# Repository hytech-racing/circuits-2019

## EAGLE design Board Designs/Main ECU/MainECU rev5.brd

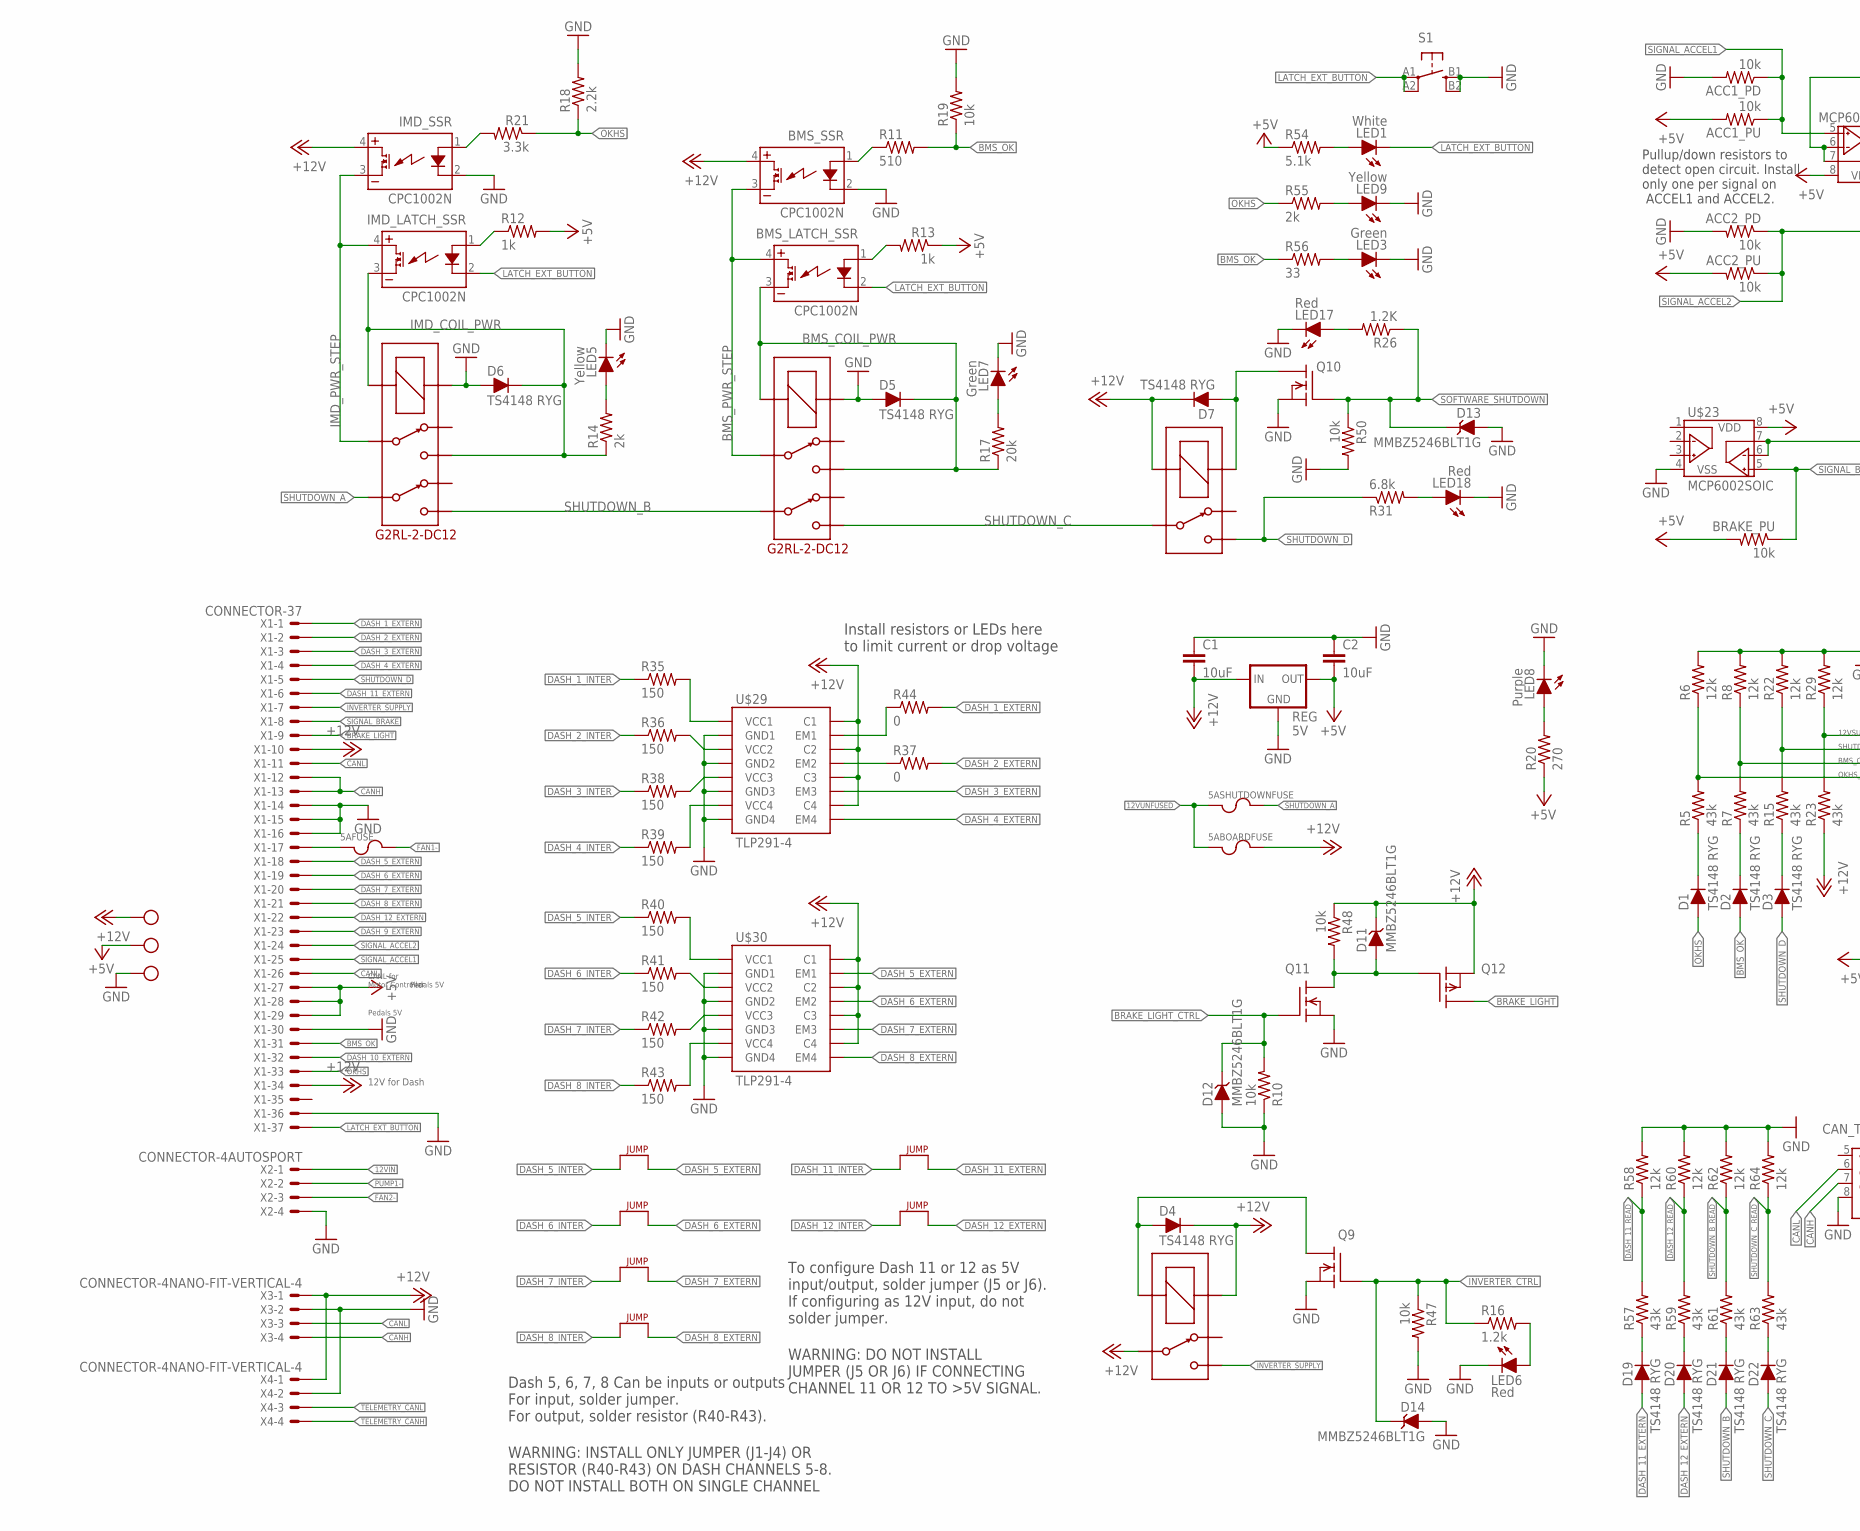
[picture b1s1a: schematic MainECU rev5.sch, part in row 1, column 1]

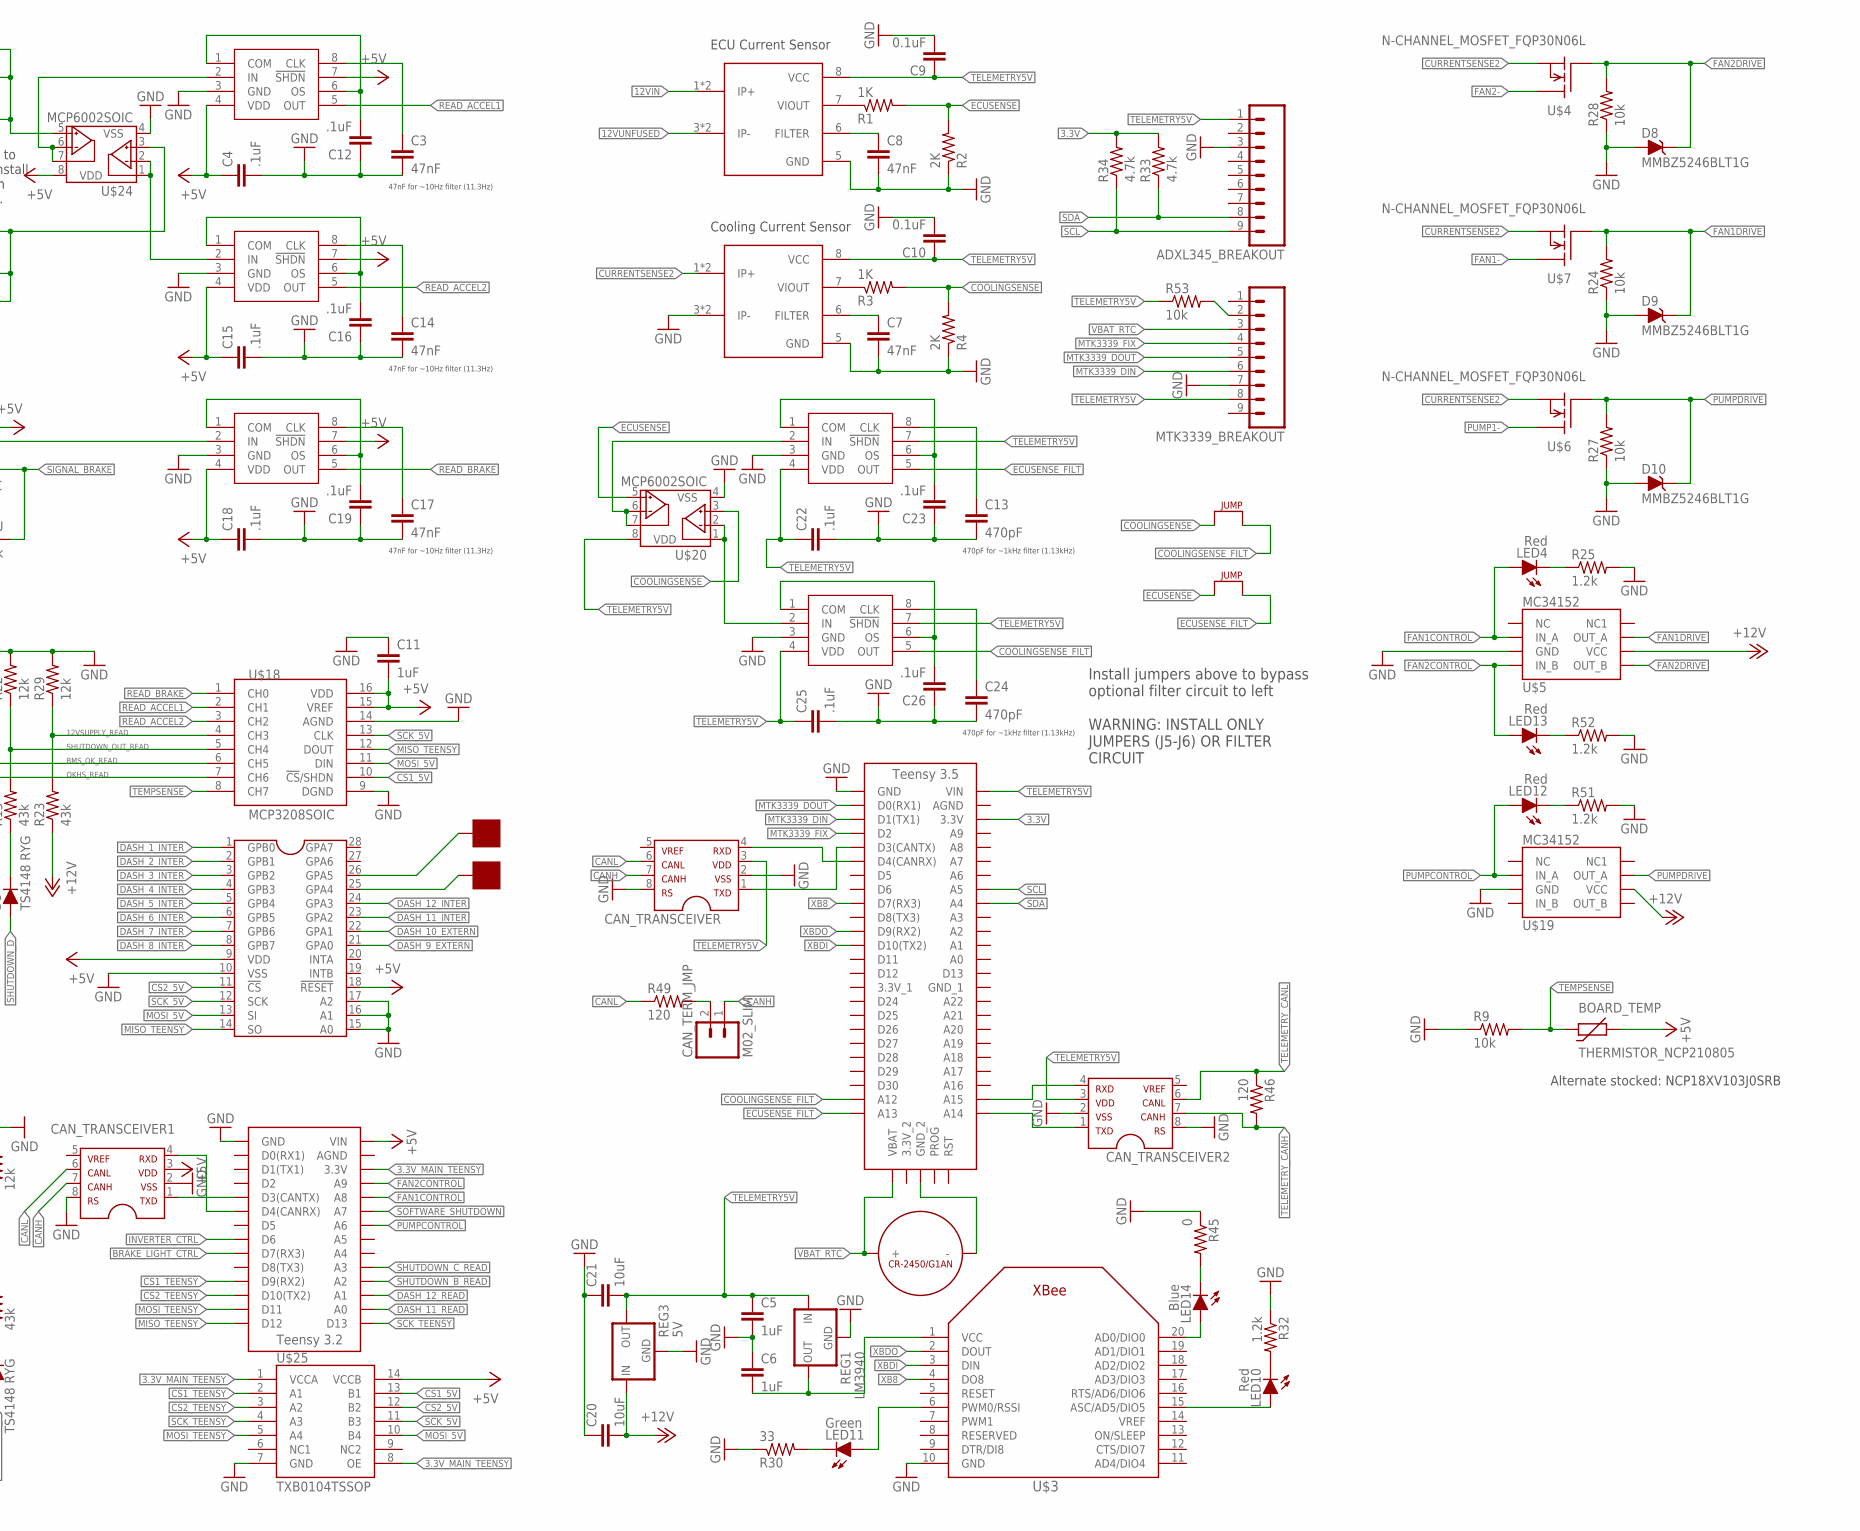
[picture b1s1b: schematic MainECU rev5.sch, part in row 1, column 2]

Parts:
5ABOARDFUSE, 5AFUSE, 5ASHUTDOWNFUSE: FUSE_MINIBLADE; MINI-BLADE_FUSE_HOLDER
ACC1_PD, ACC1_PU, ACC2_PD, ACC2_PU: 10k; 0805
ADXL345_BREAKOUT: M09; 1X09
BMS_LATCH_SSR: CPC1002N; SOP04
BMS_SSR: CPC1002N; SOP04
BOARD_TEMP: THERMISTOR_NCP210805; 0805
BRAKE_PU: 10k; 0805
C1, C2, C20, C21: 10uF; 0805
C3, C7, C8, C14, C17: 47nF; 0805
C4, C12, C15, C16, C18, C19, C22, C23, C25, C26: .1uF; 0805
C5, C6, C11: 1uF; 0805
C9, C10: 0.1uF; 0805
C13, C24: 470pF; 0805
CAN_TERM_JMP: M02_SLIM; 1X02_SLIM
CAN_TRANSCEIVER, CAN_TRANSCEIVER1, CAN_TRANSCEIVER2: MCP2551; SOIC-08
D1, D2, D3, D4, D5, D6, D7, D19, D20, D21, D22: TS4148 RYG; 0805_D
D8, D9, D10, D11, D12, D13, D14: MMBZ5246BLT1G; SOT23
IMD_LATCH_SSR: CPC1002N; SOP04
IMD_SHUTDOWN, IMD_SHUTDOWN1: G2RL-2-DC12; G2RL-2
IMD_SSR: CPC1002N; SOP04
INVERTER_PWR_RELAY: G5LE; ZF112
J1, J2, J3, J4, J5, J6, J7, J8: JUMPER; 0805
LED1: White; LED-805
LED3, LED7, LED11: Green; LED-805
LED4, LED6, LED10, LED12, LED13, LED17, LED18: Red; LED-805
LED5, LED9: Yellow; LED-805
LED8: Purple; LED-805
LED14: Blue; LED-805
MTK3339_BREAKOUT: M09; 1X09
P1, P2: SOLDER_PAD; SOLDER_PAD_XSMALL
Q9, Q10, Q11: DMG3406LSOT; SOT23
Q12: P-CHANNEL_MOSFET_DMP3099L-7; SOT23
R1, R3: 1K; 0805
R2, R4: 2K; 0805
R5, R7, R15, R23, R57, R59, R61, R63: 43k; 0805
R6, R8, R22, R29, R58, R60, R62, R64: 12k; 0805
R9, R10, R19, R24, R27, R28, R47, R48, R50, R53: 10k; 0805
R11: 510; 0805
R12, R13: 1k; 0805
R14, R55: 2k; 0805
R16, R25, R32, R51, R52: 1.2k; 0805
R17: 20k; 0805
R18: 2.2k; 0805
R20: 270; 0805
R21: 3.3k; 0805
R26: 1.2K; 0805
R30, R56: 33; 0805
R31: 6.8k; 0805
R33, R34: 4.7k; 0805
R35, R36, R38, R39, R40, R41, R42, R43: 150; 0805
R37, R44, R45: 0; 0805
R46, R49: 120; 0805
R54: 5.1k; 0805
REG, REG3: 5V; OKI-78SR
REG1: LM3940; SOT223
S1: BTN_10-XXSMD; TACTILE_SWITCH_SMD_6.2MM_TALL
SOFTWARE_SHUTOFF: G5LE; ZF112
U$1: TEENSY_3.2_SIMPLE
U$2: TEENSY_3.5_EXT
U$3: XBEE
U$4, U$6, U$7: N-CHANNEL_MOSFET_FQP30N06L; TO-220-H-HOLE
U$5, U$19: MC34152; SOIC-08
U$8, U$11, U$12: TEST_POINT
U$9, U$10: ACS715_CURRENT_SENSOR; SOP8
U$16: CR-2450/G1AN
U$17: MCP23S17SSOP28; SSOP28
U$18: MCP3208SOIC; SOIC-16
U$20, U$23, U$24: MCP6002SOIC; SOIC-08
U$21, U$22, U$26, U$27, U$28: MAX7480; SOIC-08
U$25: TXB0104TSSOP; TSSOP-14
U$29, U$30: TLP291-4; 11-11F1
X1: CONNECTOR-37; AUTOSPORT_14-35
X2: CONNECTOR-4AUTOSPORT; AUTOSPORT_12-04
X3, X4: CONNECTOR-4NANO-FIT-VERTICAL-4; NANO-FIT_VERTICAL-4

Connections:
3.3V: R33.2, R34.2, U$2.3.3V
3.3V_MAIN_TEENSY: U$1.3.3V, U$25.1 (VCCA), U$25.8 (OE)
12VIN: U$9.1 (IP+), U$9.2 (IP+), X2.P$1
12VSUPPLY_READ: R23.2, R29.1, U$18.4 (CH3)
12VUNFUSED: 5ABOARDFUSE.L1 (1), 5ABOARDFUSE.L2 (1), 5ASHUTDOWNFUSE.L1 (1), 5ASHUTDOWNFUSE.L2 (1), U$9.3 (IP-), U$9.4 (IP-)
+5V: ACC1_PU.2, ACC2_PU.2, BOARD_TEMP.1, BRAKE_PU.2, C2.2, C4.1, C11.2, C15.1, C18.1, CAN_TRANSCEIVER1.3, R12.2, R13.1, R20.1, R54.1, REG.3 (OUT), U$1.VIN, U$11.P$1, U$17.9 (VDD), U$17.18 (!RESET), U$18.15 (VREF), U$18.16 (VDD), U$23.8 (VDD), U$24.8 (VDD), U$25.14 (VCCB), U$26.4 (VDD), U$26.7 (!SHDN), U$27.4 (VDD), U$27.7 (!SHDN), U$28.4 (VDD), U$28.7 (!SHDN), X1.P$27, X1.P$28, X1.P$29
+12V: 5ABOARDFUSE.R1 (2), 5ABOARDFUSE.R2 (2), BMS_SSR.4 (DC+), C1.2, C20.2, D4.C, D7.C, D11.3 (C), IMD_SSR.4 (DC+), INVERTER_PWR_RELAY.1 (COIL+), INVERTER_PWR_RELAY.P, Q12.2 (S), R23.1, R48.1, REG.1 (IN), REG3.1 (IN), SOFTWARE_SHUTOFF.2 (COIL-), U$5.6 (VCC), U$8.P$1, U$19.6 (VCC), U$29.10 (C4), U$29.12 (C3), U$29.14 (C2), U$29.16 (C1), U$30.10 (C4), U$30.12 (C3), U$30.14 (C2), U$30.16 (C1), X1.P$10, X1.P$34, X3.P$1, X4.P$1
BMS_COIL_PWR: BMS_LATCH_SSR.3 (DC-), D5.C, IMD_SHUTDOWN1.4, IMD_SHUTDOWN1.COIL-, R17.1
BMS_OK: D2.A, R11.2, R19.1, R56.1, X1.P$31
BMS_OK_READ: R7.2, R8.1, U$18.6 (CH5)
BMS_PWR_STEP: BMS_LATCH_SSR.4 (DC+), BMS_SSR.3 (DC-), IMD_SHUTDOWN1.3
BRAKE_LIGHT: Q12.3 (D), X1.P$9
BRAKE_LIGHT_CTRL: D12.3 (C), Q11.1 (G), R10.2, U$1.D7(RX3)
CANH: CAN_TERM_JMP.1, CAN_TRANSCEIVER.7, CAN_TRANSCEIVER1.7, X1.P$12, X1.P$13, X3.P$4
CANL: CAN_TRANSCEIVER.6, CAN_TRANSCEIVER1.6, R49.1, X1.P$11, X1.P$26, X3.P$3
COOLINGSENSE: J5.2, R3.2, R4.2, U$20.3 (VINA+)
COOLINGSENSE_FILT: J5.1, U$2.A12, U$22.5 (OUT)
CS1_5V: U$18.10 (!CS!/SHDN), U$25.13 (B1)
CS1_TEENSY: U$1.D9(RX2), U$25.2 (A1)
CS2_5V: U$17.11 (!CS), U$25.12 (B2)
CS2_TEENSY: U$1.D10(TX2), U$25.3 (A2)
CURRENTSENSE2: U$4.3 (S), U$6.3 (S), U$7.3 (S), U$10.1 (IP+), U$10.2 (IP+)
DASH_1_EXTERN: R44.2, X1.P$1
DASH_1_INTER: R35.1, U$17.1 (GPB0)
DASH_2_EXTERN: R37.2, X1.P$2
DASH_2_INTER: R36.1, U$17.2 (GPB1)
DASH_3_EXTERN: U$29.11 (EM3), X1.P$3
DASH_3_INTER: R38.1, U$17.3 (GPB2)
DASH_4_EXTERN: U$29.9 (EM4), X1.P$4
DASH_4_INTER: R39.1, U$17.4 (GPB3)
DASH_5_EXTERN: J1.1, U$30.15 (EM1), X1.P$18
DASH_5_INTER: J1.2, R40.1, U$17.5 (GPB4)
DASH_6_EXTERN: J2.1, U$30.13 (EM2), X1.P$19
DASH_6_INTER: J2.2, R41.1, U$17.6 (GPB5)
DASH_7_EXTERN: J3.1, U$30.11 (EM3), X1.P$20
DASH_7_INTER: J3.2, R42.1, U$17.7 (GPB6)
DASH_8_EXTERN: J4.1, U$30.9 (EM4), X1.P$21
DASH_8_INTER: J4.2, R43.1, U$17.8 (GPB7)
DASH_9_EXTERN: U$17.21 (GPA0), X1.P$23
DASH_10_EXTERN: U$17.22 (GPA1), X1.P$32
DASH_11_EXTERN: D19.A, J8.1, X1.P$6
DASH_11_INTER: J8.2, U$17.23 (GPA2)
DASH_11_READ: R57.2, R58.1, U$1.A0
DASH_12_EXTERN: D20.A, J7.1, X1.P$22
DASH_12_INTER: J7.2, U$17.24 (GPA3)
DASH_12_READ: R59.2, R60.1, U$1.A1
ECUSENSE: J6.2, R1.2, R2.2, U$20.5 (VINB+)
ECUSENSE_FILT: J6.1, U$2.A13, U$21.5 (OUT)
FAN1-: 5AFUSE.R1 (2), 5AFUSE.R2 (2), U$7.2 (D)
FAN1CONTROL: LED4.A, U$1.A8, U$5.2 (IN_A)
FAN1DRIVE: D9.3 (C), R24.2, U$5.7 (OUT_A), U$7.1 (G)
FAN2-: U$4.2 (D), X2.P$3
FAN2CONTROL: LED13.A, U$1.A9, U$5.4 (IN_B)
FAN2DRIVE: D8.3 (C), R28.2, U$4.1 (G), U$5.5 (OUT_B)
GND: ACC1_PD.2, ACC2_PD.2, ADXL345_BREAKOUT.3, BMS_SSR.2 (CONTROL-), C1.1, C2.1, C3.2, C4.2, C5.2, C6.1, C7.2, C8.2, C9.2, C10.2, C11.1, C12.1, C13.2, C14.2, C15.2, C16.1, C17.2, C18.2, C19.1, C20.1, C21.1, C22.2, C23.1, C24.2, C25.2, C26.1, CAN_TRANSCEIVER.2, CAN_TRANSCEIVER.8, CAN_TRANSCEIVER1.2, CAN_TRANSCEIVER1.8, CAN_TRANSCEIVER2.2, CAN_TRANSCEIVER2.8, D5.A, D6.A, D8.1 (A), D9.1 (A), D10.1 (A), D12.1 (A), D13.1 (A), D14.1 (A), IMD_SHUTDOWN.COIL+, IMD_SHUTDOWN1.COIL+, IMD_SSR.2 (CONTROL-), LED3.C, LED5.C, LED6.C, LED7.C, LED8.C, LED9.C, LED17.C, LED18.C, MTK3339_BREAKOUT.7, Q9.2 (S), Q10.2 (S), Q11.2 (S), R2.1, R4.1, R6.2, R8.2, R9.1, R10.1, R18.2, R19.2, R22.2, R24.1, R25.2, R27.1, R28.1, R29.2, R30.1, R32.1, R45.1, R47.2, R50.2, R51.2, R52.2, R58.2, R60.2, R62.2, R64.2, REG.2 (GND), REG1.2 (GND), REG1.4 (GND), REG3.2 (GND), S1.B1 (S), S1.B2 (S1), U$1.GND, U$2.GND, U$3.10 (GND), U$5.3 (GND), U$9.5 (GND), U$10.3 (IP-), U$10.4 (IP-), U$10.5 (GND), U$12.P$1, U$17.10 (VSS), U$17.15 (A0), U$17.16 (A1), U$17.17 (A2), U$18.9 (DGND), U$18.14 (AGND), U$19.3 (GND), U$20.4 (VSS), U$21.3 (GND), U$22.3 (GND), U$23.4 (VSS), U$24.4 (VSS), U$25.7 (GND), U$26.3 (GND), U$27.3 (GND), U$28.3 (GND), U$29.2 (GND1), U$29.4 (GND2), U$29.6 (GND3), U$29.8 (GND4), U$30.2 (GND1), U$30.4 (GND2), U$30.6 (GND3), U$30.8 (GND4), X1.P$14, X1.P$15, X1.P$16, X1.P$30, X1.P$36, X2.P$4, X3.P$2, X4.P$2
IMD_COIL_PWR: D6.C, IMD_LATCH_SSR.3 (DC-), IMD_SHUTDOWN.4, IMD_SHUTDOWN.COIL-, R14.1
IMD_PWR_STEP: IMD_LATCH_SSR.4 (DC+), IMD_SHUTDOWN.3, IMD_SSR.3 (DC-)
INVERTER_CTRL: D14.3 (C), Q9.1 (G), R16.1, R47.1, U$1.D6
INVERTER_SUPPLY: INVERTER_PWR_RELAY.S, X1.P$7
LATCH_EXT_BUTTON: BMS_LATCH_SSR.2 (CONTROL-), IMD_LATCH_SSR.2 (CONTROL-), LED1.C, S1.A1, S1.A2 (P1), X1.P$37
MISO_TEENSY: U$1.D12, U$17.14 (SO), U$18.12 (DOUT)
MOSI_5V: U$17.13 (SI), U$18.11 (DIN), U$25.10 (B4)
MOSI_TEENSY: U$1.D11, U$25.5 (A4)
MTK3339_DIN: MTK3339_BREAKOUT.6, U$2.D1(TX1)
MTK3339_DOUT: MTK3339_BREAKOUT.5, U$2.D0(RX1)
MTK3339_FIX: MTK3339_BREAKOUT.4, U$2.D2
unnamed: 5AFUSE.L1 (1), 5AFUSE.L2 (1), X1.P$17
unnamed: LED1.A, R54.2
unnamed: R1.1, U$9.7 (VIOUT)
unnamed: C12.2, U$27.1 (COM), U$27.6 (OS)
unnamed: IMD_LATCH_SSR.1 (CONTROL+), R12.1
unnamed: R3.1, U$10.7 (VIOUT)
unnamed: MTK3339_BREAKOUT.2, R53.2
unnamed: C8.1, U$9.6 (FILTER)
unnamed: LED3.A, R56.2
unnamed: D1.C, R5.1
unnamed: D2.C, R7.1
unnamed: BMS_LATCH_SSR.1 (CONTROL+), R13.2
unnamed: CAN_TRANSCEIVER.4, U$2.D4(CANRX)
unnamed: CAN_TRANSCEIVER.1, U$2.D3(CANTX)
unnamed: CAN_TRANSCEIVER1.4, U$1.D4(CANRX)
unnamed: D19.C, R57.1
unnamed: CAN_TERM_JMP.2, R49.2
unnamed: BMS_SSR.1 (CONTROL+), R11.1
unnamed: LED5.A, R14.2
unnamed: U$20.1 (VOUTA), U$20.2 (VINA-), U$22.2 (IN)
unnamed: C3.1, U$27.8 (CLK)
unnamed: CAN_TRANSCEIVER1.1, U$1.D3(CANTX)
unnamed: U$24.1 (VOUTA), U$24.2 (VINA-), U$28.2 (IN)
unnamed: U$24.6 (VINB-), U$24.7 (VOUTB), U$27.2 (IN)
unnamed: U$23.6 (VINB-), U$23.7 (VOUTB), U$26.2 (IN)
unnamed: LED9.A, R55.2
unnamed: D7.A, Q10.3 (D), SOFTWARE_SHUTOFF.1 (COIL+)
unnamed: LED6.A, R16.2
unnamed: LED8.A, R20.2
unnamed: R36.2, U$29.3 (VCC2)
unnamed: IMD_SSR.1 (CONTROL+), R21.2
unnamed: LED7.A, R17.2
unnamed: D3.C, R15.1
unnamed: D20.C, R59.1
unnamed: LED14.C, R45.2
unnamed: C16.2, U$28.1 (COM), U$28.6 (OS)
unnamed: C19.2, U$26.1 (COM), U$26.6 (OS)
unnamed: C14.1, U$28.8 (CLK)
unnamed: U$20.6 (VINB-), U$20.7 (VOUTB), U$21.2 (IN)
unnamed: LED18.A, R31.2
unnamed: C17.1, U$26.8 (CLK)
unnamed: R37.1, U$29.13 (EM2)
unnamed: C23.2, U$21.1 (COM), U$21.6 (OS)
unnamed: C13.1, U$21.8 (CLK)
unnamed: LED11.C, R30.2
unnamed: LED17.A, R26.2
unnamed: LED11.A, U$3.6 (PWM0/RSSI)
unnamed: C7.1, U$10.6 (FILTER)
unnamed: LED10.A, U$3.15 (ASC/AD5/DIO5)
unnamed: LED10.C, R32.2
unnamed: R35.2, U$29.1 (VCC1)
unnamed: R38.2, U$29.5 (VCC3)
unnamed: R39.2, U$29.7 (VCC4)
unnamed: R40.2, U$30.1 (VCC1)
unnamed: R41.2, U$30.3 (VCC2)
unnamed: R42.2, U$30.5 (VCC3)
unnamed: R43.2, U$30.7 (VCC4)
unnamed: D11.1 (A), Q11.3 (D), Q12.1 (G), R48.2
unnamed: R44.1, U$29.15 (EM1)
unnamed: D21.C, R61.1
unnamed: U$2.GND_2, U$16.-
unnamed: CAN_TRANSCEIVER2.4, U$2.A15
unnamed: LED14.A, U$3.20 (AD0/DIO0)
unnamed: CAN_TRANSCEIVER2.1, U$2.A14
unnamed: D22.C, R63.1
unnamed: D4.A, INVERTER_PWR_RELAY.2 (COIL-), Q9.3 (D)
unnamed: C26.2, U$22.1 (COM), U$22.6 (OS)
unnamed: C24.1, U$22.8 (CLK)
unnamed: LED4.C, R25.1
unnamed: LED12.C, R51.1
unnamed: LED13.C, R52.1
unnamed: P1.P$1, U$17.25 (GPA4)
unnamed: P2.P$1, U$17.26 (GPA5)
OKHS: D1.A, R18.1, R21.1, R55.1, X1.P$33
OKHS_READ: R5.2, R6.1, U$18.7 (CH6)
PUMP1-: U$6.2 (D), X2.P$2
PUMPCONTROL: LED12.A, U$1.A6, U$19.2 (IN_A)
PUMPDRIVE: D10.3 (C), R27.2, U$6.1 (G), U$19.7 (OUT_A)
READ_ACCEL1: U$18.2 (CH1), U$27.5 (OUT)
READ_ACCEL2: U$18.3 (CH2), U$28.5 (OUT)
READ_BRAKE: U$18.1 (CH0), U$26.5 (OUT)
SCK_5V: U$17.12 (SCK), U$18.13 (CLK), U$25.11 (B3)
SCK_TEENSY: U$1.D13, U$25.4 (A3)
SCL: ADXL345_BREAKOUT.9, R34.1, U$2.A5
SDA: ADXL345_BREAKOUT.8, R33.1, U$2.A4
SHUTDOWN_A: 5ASHUTDOWNFUSE.R1 (2), 5ASHUTDOWNFUSE.R2 (2), IMD_SHUTDOWN.6
SHUTDOWN_B: D21.A, IMD_SHUTDOWN.5, IMD_SHUTDOWN1.6
SHUTDOWN_B_READ: R61.2, R62.1, U$1.A2
SHUTDOWN_C: D22.A, IMD_SHUTDOWN1.5, SOFTWARE_SHUTOFF.P
SHUTDOWN_C_READ: R63.2, R64.1, U$1.A3
SHUTDOWN_D: D3.A, R31.1, SOFTWARE_SHUTOFF.S, X1.P$5
SHUTDOWN_OUT_READ: R15.2, R22.1, U$18.5 (CH4)
SIGNAL_ACCEL1: ACC1_PD.1, ACC1_PU.1, U$24.5 (VINB+), X1.P$25
SIGNAL_ACCEL2: ACC2_PD.1, ACC2_PU.1, U$24.3 (VINA+), X1.P$24
SIGNAL_BRAKE: BRAKE_PU.1, U$23.5 (VINB+), X1.P$8
SOFTWARE_SHUTDOWN: D13.3 (C), Q10.1 (G), R26.1, R50.1, U$1.A7
TELEMETRY5V: ADXL345_BREAKOUT.1, C5.1, C9.1, C10.1, C21.2, C22.1, C25.1, CAN_TRANSCEIVER.3, CAN_TRANSCEIVER2.3, MTK3339_BREAKOUT.8, R53.1, REG1.1 (IN), REG3.3 (OUT), U$2.VIN, U$9.8 (VCC), U$10.8 (VCC), U$20.8 (VDD), U$21.4 (VDD), U$21.7 (!SHDN), U$22.4 (VDD), U$22.7 (!SHDN)
TELEMETRY_CANH: CAN_TRANSCEIVER2.7, R46.2, X4.P$4
TELEMETRY_CANL: CAN_TRANSCEIVER2.6, R46.1, X4.P$3
TEMPSENSE: BOARD_TEMP.2, R9.2, U$18.8 (CH7)
VBAT_RTC: MTK3339_BREAKOUT.3, U$2.VBAT, U$16.+_0 (+), U$16.+_1 (+)
VCC: C6.2, REG1.3 (OUT), U$3.1 (VCC)
XB8: U$2.D7(RX3), U$3.4 (DO8)
XBDI: U$2.D10(TX2), U$3.3 (DIN)
XBDO: U$2.D9(RX2), U$3.2 (DOUT)

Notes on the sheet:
ECU Current Sensor
Cooling Current Sensor
Pullup/down resistors to detect open circuit. Install only one per signal on ACCEL1 and ACCEL2.
Pedals 5V
CANL for Motor Controller
47nF for ~10Hz filter (11.3Hz)
12V for Dash
Dash 5, 6, 7, 8 Can be inputs or outputs For input, solder jumper. For output, solder resistor (R40-R43).
470pF for ~1kHz filter (1.13kHz)
Install resistors or LEDs here to limit current or drop voltage
WARNING: INSTALL ONLY JUMPER (J1-J4) OR RESISTOR (R40-R43) ON DASH CHANNELS 5-8. DO NOT INSTALL BOTH ON SINGLE CHANNEL
Alternate stocked: NCP18XV103J0SRB
Install jumpers above to bypass optional filter circuit to left WARNING: INSTALL ONLY JUMPERS (J5-J6) OR FILTER CIRCUIT
To configure Dash 11 or 12 as 5V input/output, solder jumper (J5 or J6). If configuring as 12V input, do not solder jumper.
WARNING: DO NOT INSTALL JUMPER (J5 OR J6) IF CONNECTING CHANNEL 11 OR 12 TO >5V SIGNAL.

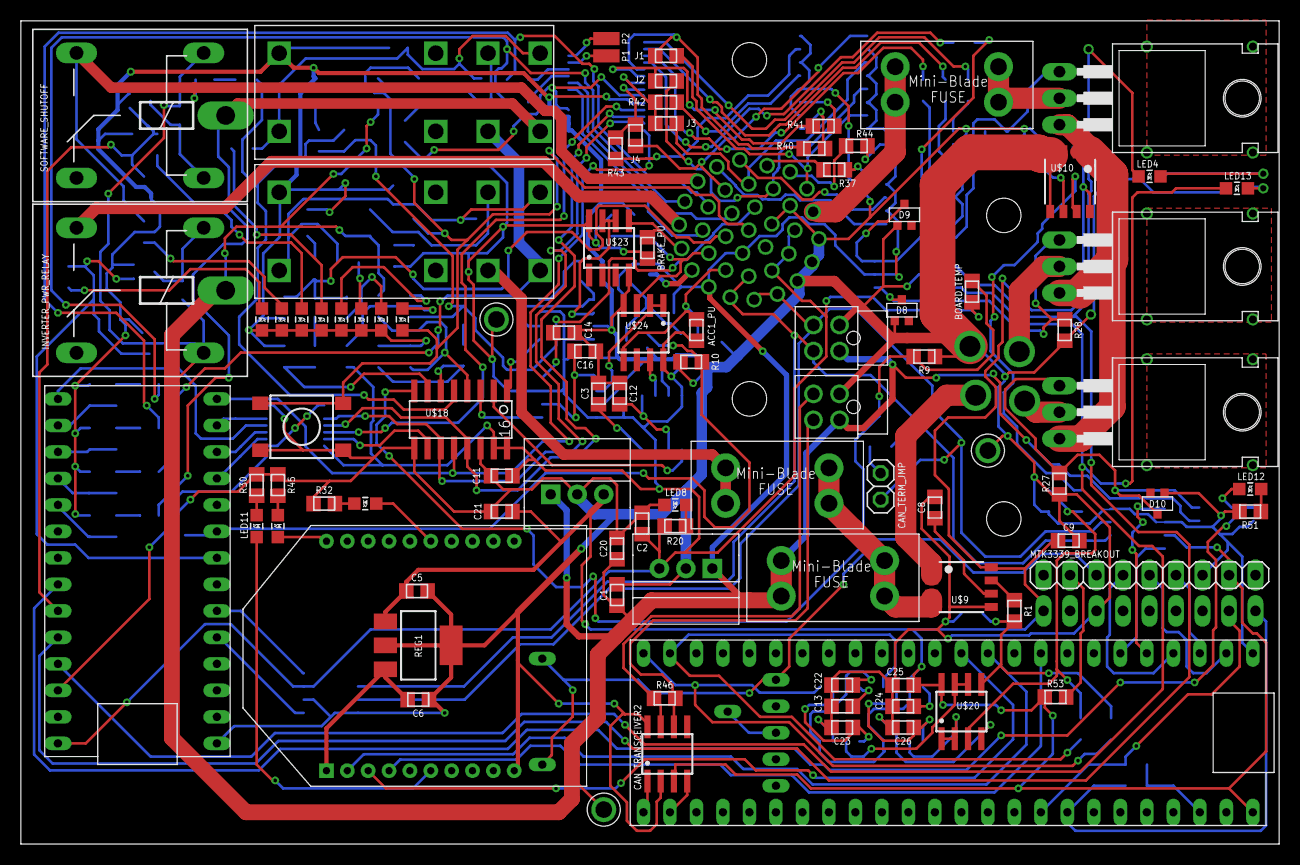
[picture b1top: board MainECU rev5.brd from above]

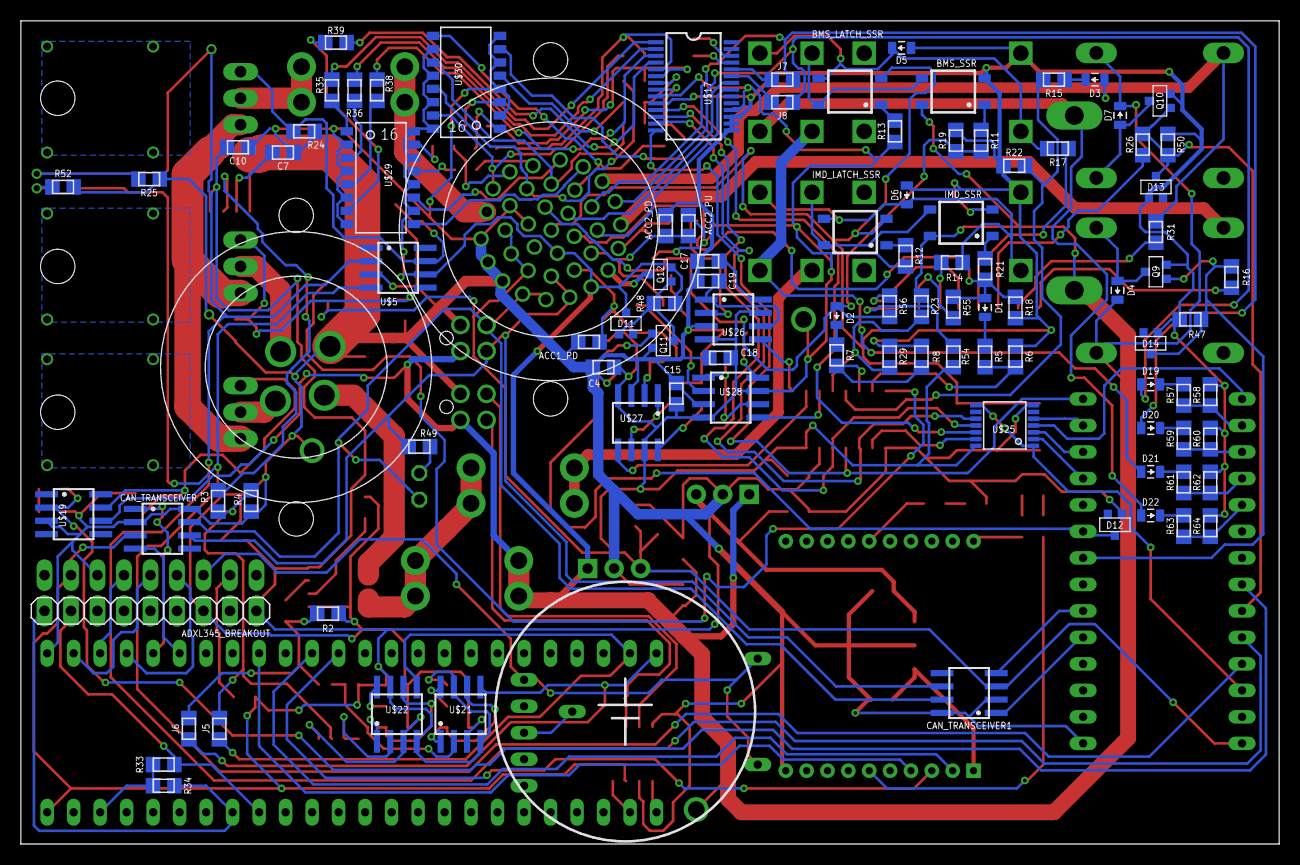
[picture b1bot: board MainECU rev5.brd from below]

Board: 2 copper layers, 120.6 x 78.9 mm, 195 parts (100 on the bottom side), 171 nets.

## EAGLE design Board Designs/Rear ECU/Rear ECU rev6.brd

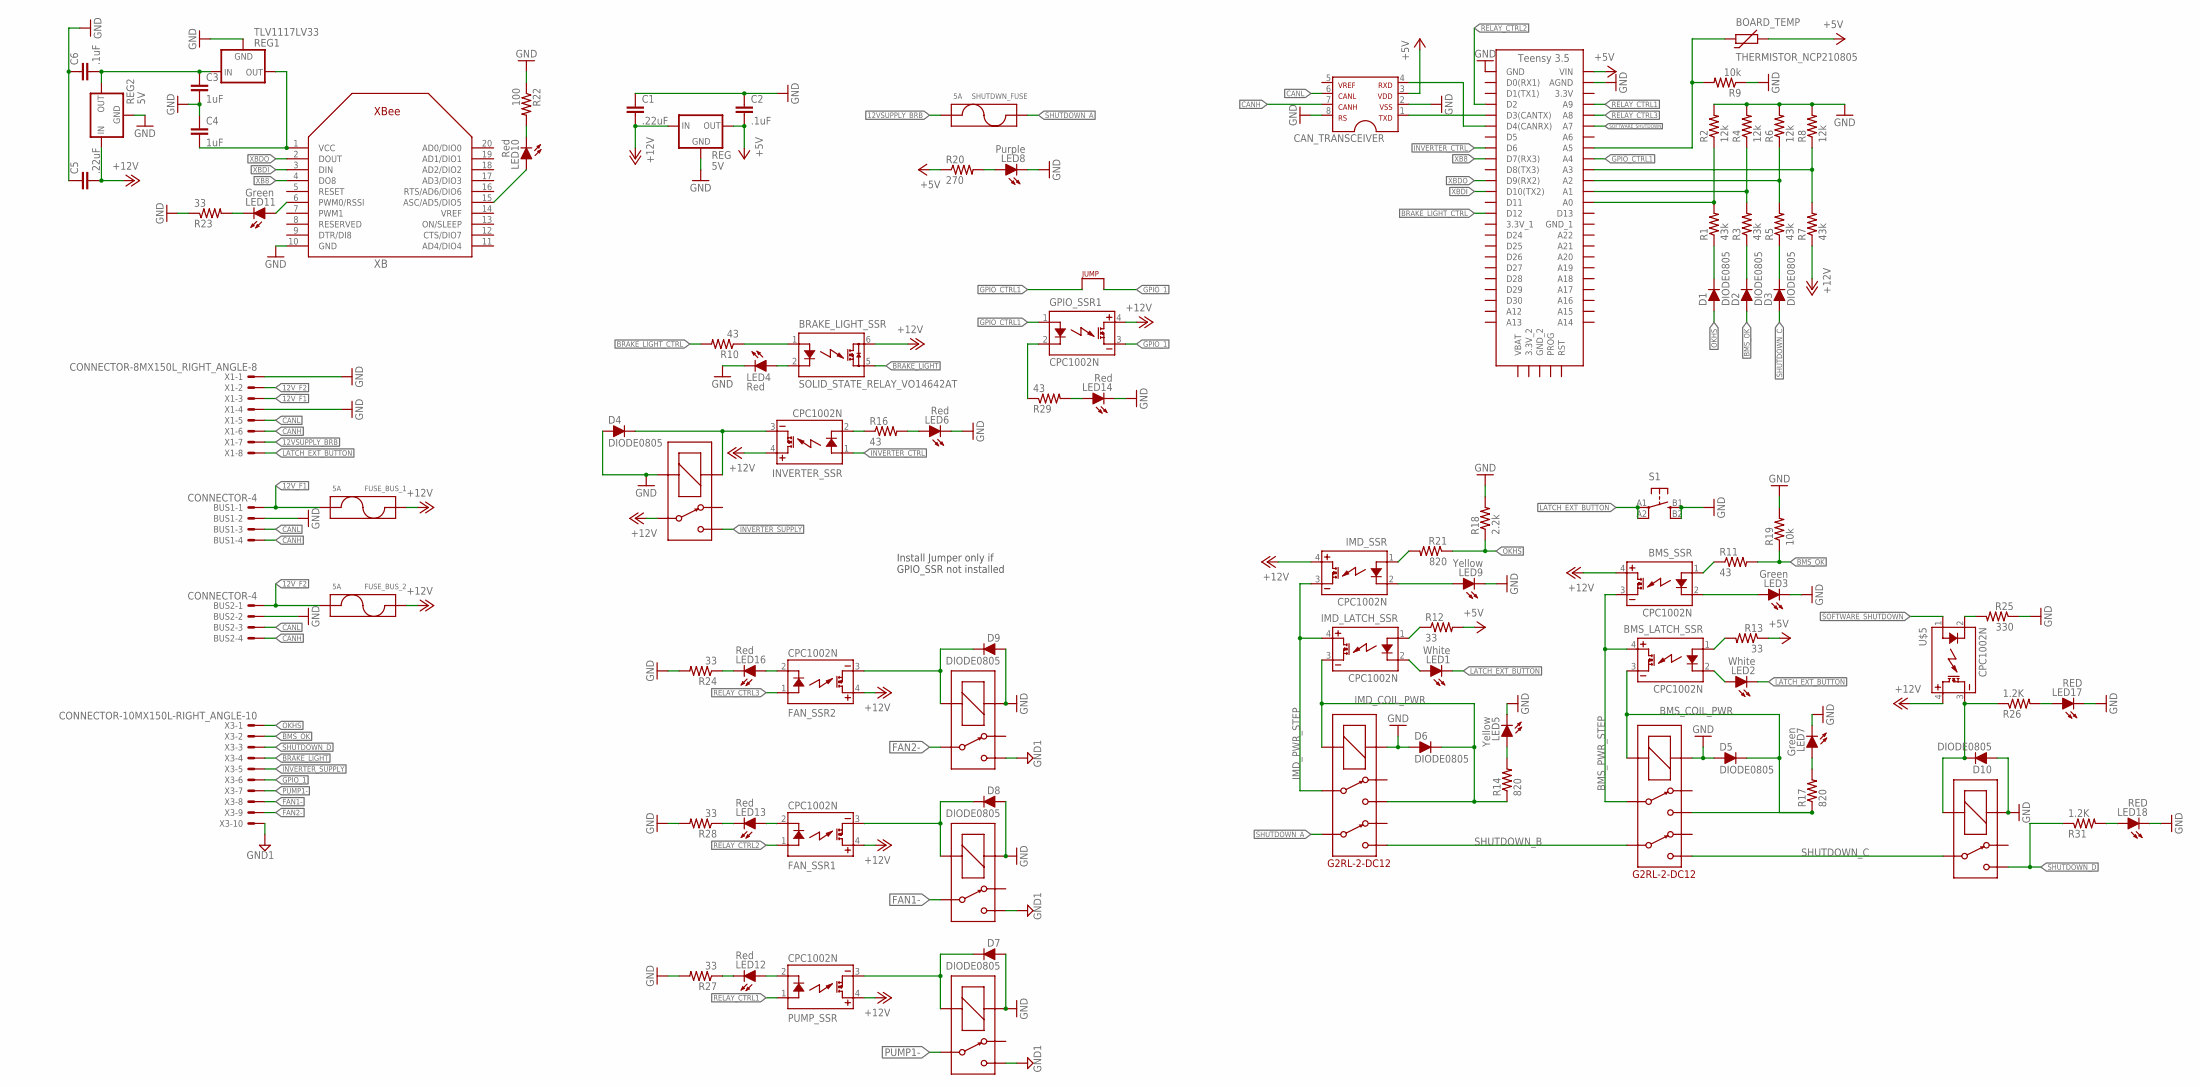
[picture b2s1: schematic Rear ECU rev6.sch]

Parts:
BMS_LATCH_SSR: CPC1002N; SOP04
BMS_SSR: CPC1002N; SOP04
BOARD_TEMP: THERMISTOR_NCP210805; 0805
BRAKE_LIGHT_SSR: SOLID_STATE_RELAY_VO14642AT; DIL06
BUS1, BUS2: CONNECTOR-4; MINIFIT_5566-4
C1, C5: .22uF; 0805
C2, C6: .1uF; 0805
C3, C4: 1uF; 0805
CAN_TRANSCEIVER: MCP2551; SOIC-08
D1, D2, D3, D4, D5, D6, D7, D8, D9, D10: DIODE0805; 0805_D
FAN_SSR1, FAN_SSR2: CPC1002N; SOP04
FUSE_BUS_1, FUSE_BUS_2: 5A; MINI-BLADE_FUSE_HOLDER
GPIO_SSR1: CPC1002N; SOP04
IMD_LATCH_SSR: CPC1002N; SOP04
IMD_SHUTDOWN, IMD_SHUTDOWN1: G2RL-2-DC12; G2RL-2
IMD_SSR: CPC1002N; SOP04
INVERTER_SSR: CPC1002N; SOP04
LED1, LED2: White; LED-805
LED3, LED7, LED11: Green; LED-805
LED4, LED6, LED10, LED12, LED13, LED14, LED16: Red; LED-805
LED5, LED9: Yellow; LED-805
LED8: Purple; LED-805
LED17, LED18: RED; LED-805
PUMP_SSR: CPC1002N; SOP04
R1, R3, R5, R7: 43k; 0805
R2, R4, R6, R8: 12k; 0805
R9, R19: 10k; 0805
R10, R11, R16, R29: 43; 0805
R12, R13, R23, R24, R27, R28: 33; 0805
R14, R17, R21: 820; 0805
R18: 2.2k; 0805
R20: 270; 0805
R22: 100; 0805
R25: 330; 0805
R26, R31: 1.2K; 0805
REG, REG2: 5V; SOT223
REG1: TLV1117LV33; SOT223
S1: BTN_10-XXSMD; TACTILE_SWITCH_SMD_6.2MM_TALL
SHUTDWN_FUSE: 5A; MINI-BLADE_FUSE_HOLDER
SOFTWARE_SHUTOFF: G5LE; ZF112
U$1, U$2, U$6, U$7: G5LE; ZF112
U$4: TEENSY_3.5_EXT
U$5: CPC1002N; SOP04
U$10: JUMPER; 0805
X1: CONNECTOR-8MX150L_RIGHT_ANGLE-8; MX150L_RIGHT_ANGLE-8
X3: CONNECTOR-10MX150L-RIGHT_ANGLE-10; MX150L_RIGHT_ANGLE-10
XB: XBEE

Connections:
12VSUPPLY_BRB: SHUTDWN_FUSE.R1 (P2), SHUTDWN_FUSE.R2 (P2), X1.7
12VSUPPLY_READ: R7.2, R8.1, U$4.A3
12V_F1: BUS1.1, FUSE_BUS_1.R1 (P2), FUSE_BUS_1.R2 (P2), X1.3
12V_F2: BUS2.1, FUSE_BUS_2.R1 (P2), FUSE_BUS_2.R2 (P2), X1.2
+5V: BOARD_TEMP.1, C2.2, CAN_TRANSCEIVER.3, R12.2, R13.1, R20.1, REG.3 (OUT), U$4.VIN
+12V: BMS_SSR.4 (DC+), BRAKE_LIGHT_SSR.6 (IO1), C1.2, C5.2, FAN_SSR1.4 (DC+), FAN_SSR2.4 (DC+), FUSE_BUS_1.L1 (P1), FUSE_BUS_1.L2 (P1), FUSE_BUS_2.L1 (P1), FUSE_BUS_2.L2 (P1), GPIO_SSR1.4 (DC+), IMD_SSR.4 (DC+), INVERTER_SSR.4 (DC+), PUMP_SSR.4 (DC+), R7.1, REG.1 (IN), REG2.1 (IN), U$1.P, U$5.4 (DC+)
BMS_COIL_PWR: BMS_LATCH_SSR.3 (DC-), D5.C, IMD_SHUTDOWN1.4, IMD_SHUTDOWN1.COIL-, R17.1
BMS_OK: D2.A, R11.2, R19.1, X3.2
BMS_OK_READ: R3.2, R4.1, U$4.A1
BMS_PWR_STEP: BMS_LATCH_SSR.4 (DC+), BMS_SSR.3 (DC-), IMD_SHUTDOWN1.3
BRAKE_LIGHT: BRAKE_LIGHT_SSR.5 (IO2), X3.4
BRAKE_LIGHT_CTRL: R10.2, U$4.D12
CANH: BUS1.4, BUS2.4, CAN_TRANSCEIVER.7, X1.6
CANL: BUS1.3, BUS2.3, CAN_TRANSCEIVER.6, X1.5
FAN1-: U$7.P, X3.8
FAN2-: U$2.P, X3.9
GND: BUS1.2, BUS2.2, C1.1, C2.1, C3.2, C4.1, C5.1, C6.1, CAN_TRANSCEIVER.2, CAN_TRANSCEIVER.8, D4.A, D5.A, D6.A, D7.A, D8.A, D9.A, D10.A, IMD_SHUTDOWN.COIL+, IMD_SHUTDOWN1.COIL+, LED3.C, LED4.C, LED5.C, LED6.C, LED7.C, LED8.C, LED9.C, LED14.C, LED17.C, LED18.C, R2.2, R4.2, R6.2, R8.2, R9.1, R18.2, R19.2, R22.1, R23.1, R24.2, R25.1, R27.2, R28.2, REG.2 (GND), REG.4 (GND), REG1.1 (GND), REG2.2 (GND), REG2.4 (GND), S1.B1 (S), S1.B2 (S1), SOFTWARE_SHUTOFF.1 (COIL+), U$1.2 (COIL-), U$2.1 (COIL+), U$4.AGND, U$4.GND, U$6.1 (COIL+), U$7.1 (COIL+), X1.1, X1.4, XB.10 (GND)
GND1: U$2.S, U$6.S, U$7.S, X3.10
GPIO_1: GPIO_SSR1.3 (DC-), U$10.2, X3.6
GPIO_CTRL1: GPIO_SSR1.1 (CONTROL+), U$4.A4, U$10.1
IMD_COIL_PWR: D6.C, IMD_LATCH_SSR.3 (DC-), IMD_SHUTDOWN.4, IMD_SHUTDOWN.COIL-, R14.1
IMD_PWR_STEP: IMD_LATCH_SSR.4 (DC+), IMD_SHUTDOWN.3, IMD_SSR.3 (DC-)
INVERTER_CTRL: INVERTER_SSR.1 (CONTROL+), U$4.D6
INVERTER_SUPPLY: U$1.S, X3.5
LATCH_EXT_BUTTON: LED1.C, LED2.C, S1.A1, S1.A2 (P1), X1.8
unnamed: IMD_LATCH_SSR.2 (CONTROL-), LED1.A
unnamed: CAN_TRANSCEIVER.4, U$4.D4(CANRX)
unnamed: CAN_TRANSCEIVER.1, U$4.D3(CANTX)
unnamed: D7.C, PUMP_SSR.3 (DC-), U$6.2 (COIL-)
unnamed: IMD_LATCH_SSR.1 (CONTROL+), R12.1
unnamed: GPIO_SSR1.2 (CONTROL-), R29.1
unnamed: BRAKE_LIGHT_SSR.2 (LED-), LED4.A
unnamed: BMS_SSR.2 (CONTROL-), LED3.A
unnamed: LED10.A, XB.15 (ASC/AD5/DIO5)
unnamed: LED10.C, R22.2
unnamed: BMS_LATCH_SSR.1 (CONTROL+), R13.2
unnamed: LED14.A, R29.2
unnamed: BOARD_TEMP.2, R9.2, U$4.A5
unnamed: BMS_LATCH_SSR.2 (CONTROL-), LED2.A
unnamed: BRAKE_LIGHT_SSR.1 (LED+), R10.1
unnamed: BMS_SSR.1 (CONTROL+), R11.1
unnamed: LED5.A, R14.2
unnamed: D8.C, FAN_SSR1.3 (DC-), U$7.2 (COIL-)
unnamed: D9.C, FAN_SSR2.3 (DC-), U$2.2 (COIL-)
unnamed: D1.C, R1.1
unnamed: D2.C, R3.1
unnamed: D3.C, R5.1
unnamed: LED11.A, XB.6 (PWM0/RSSI)
unnamed: D4.C, INVERTER_SSR.3 (DC-), U$1.1 (COIL+)
unnamed: INVERTER_SSR.2 (CONTROL-), R16.1
unnamed: LED6.A, R16.2
unnamed: LED8.A, R20.2
unnamed: LED16.C, R24.1
unnamed: IMD_SSR.1 (CONTROL+), R21.2
unnamed: LED7.A, R17.2
unnamed: LED11.C, R23.2
unnamed: IMD_SSR.2 (CONTROL-), LED9.A
unnamed: C3.1, C6.2, REG1.3 (IN), REG2.3 (OUT)
unnamed: LED13.C, R28.1
unnamed: LED12.C, R27.1
unnamed: LED12.A, PUMP_SSR.2 (CONTROL-)
unnamed: FAN_SSR2.2 (CONTROL-), LED16.A
unnamed: LED18.A, R31.2
unnamed: FAN_SSR1.2 (CONTROL-), LED13.A
unnamed: D10.C, R26.1, SOFTWARE_SHUTOFF.2 (COIL-), U$5.3 (DC-)
unnamed: R25.2, U$5.2 (CONTROL-)
unnamed: LED17.A, R26.2
OKHS: D1.A, R18.1, R21.1, X3.1
OKHS_READ: R1.2, R2.1, U$4.A0
PUMP1-: U$6.P, X3.7
RELAY_CTRL1: PUMP_SSR.1 (CONTROL+), U$4.A9
RELAY_CTRL2: FAN_SSR1.1 (CONTROL+), U$4.D2
RELAY_CTRL3: FAN_SSR2.1 (CONTROL+), U$4.A8
SHUTDOWN_A: IMD_SHUTDOWN.6, SHUTDWN_FUSE.L1 (P1), SHUTDWN_FUSE.L2 (P1)
SHUTDOWN_B: IMD_SHUTDOWN.5, IMD_SHUTDOWN1.6
SHUTDOWN_C: D3.A, IMD_SHUTDOWN1.5, SOFTWARE_SHUTOFF.P
SHUTDOWN_D: R31.1, SOFTWARE_SHUTOFF.S, X3.3
SHUTDOWN_OUT_READ: R5.2, R6.1, U$4.A2
SOFTWARE_SHUTDOWN: U$4.A7, U$5.1 (CONTROL+)
VCC: C4.2, REG1.2 (OUT), REG1.4 (OUT), XB.1 (VCC)
XB8: U$4.D7(RX3), XB.4 (DO8)
XBDI: U$4.D10(TX2), XB.3 (DIN)
XBDO: U$4.D9(RX2), XB.2 (DOUT)

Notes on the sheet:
Install Jumper only if GPIO_SSR not installed
